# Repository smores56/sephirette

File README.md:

> **Moved.** This board now lives in the [Clog family repo](https://github.com/smores56/clog), under [`sephirette/`](https://github.com/smores56/clog/tree/main/sephirette).

---

The Sephirette
==============

The Sephirette is a split 34-key keyboard with pinky clusters. It is the split
version of the [Osprette MX][osprette-mx], designed by me, which itself was inspired by
the [Balbuzard][balbuzard] by brow.

Follow the [build guide][build-guide] to build your Sephirette.

[osprette-mx]: https://github.com/smores56/osprette-mx
[balbuzard]: https://github.com/brow/balbuzard
[build-guide]: ./doc/buildguide_en.md

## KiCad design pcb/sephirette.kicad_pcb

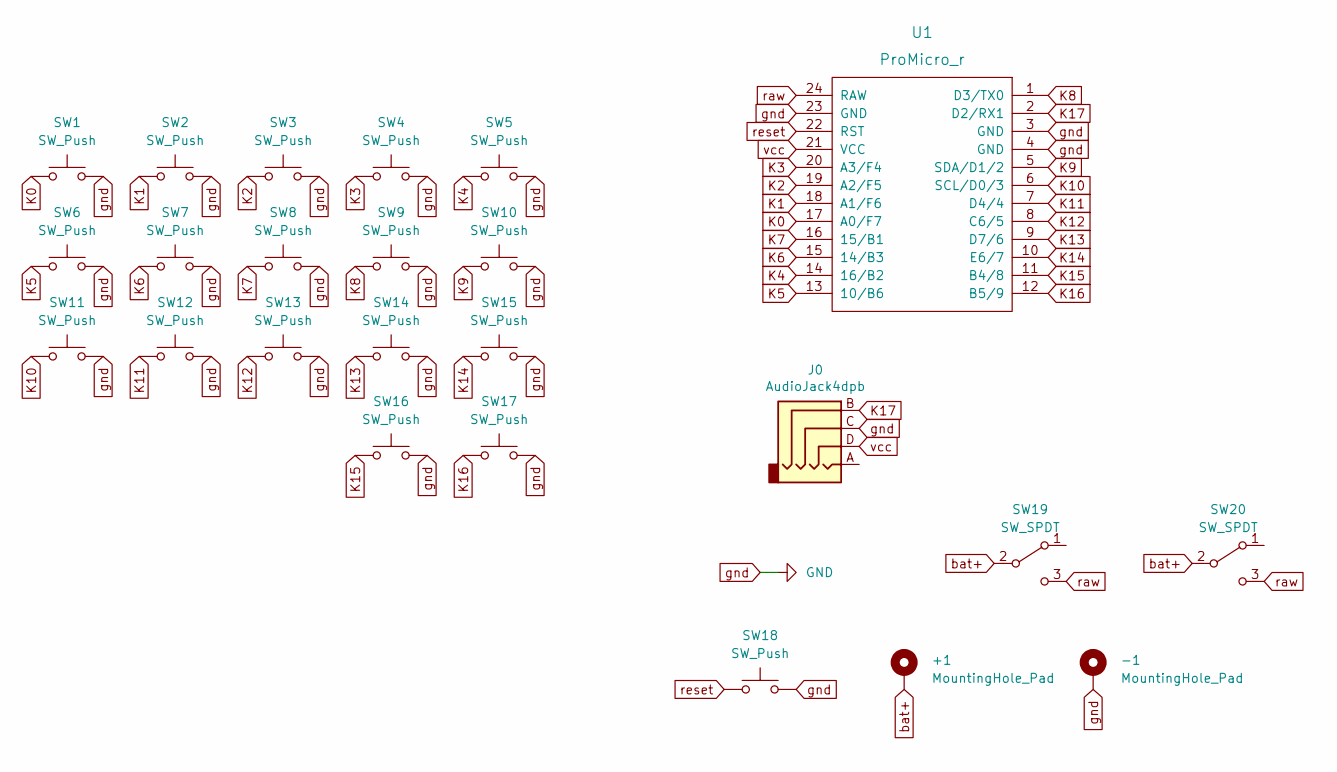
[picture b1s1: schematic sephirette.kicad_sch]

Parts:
+1: MountingHole_Pad; 1pin_conn
-1: MountingHole_Pad; 1pin_conn
J0: AudioJack4dpb; MJ-4PP-9
SW1, SW2, SW3, SW4, SW5, SW6, SW7, SW8, SW9, SW10, SW11, SW12, SW13, SW14, SW15, SW16, SW17: SW_Push; Kailh_socket_MX_optional_reversible
SW18: SW_Push; ResetSW
SW19, SW20: SW_SPDT; SW_SPDT_PCM12
U1: ProMicro_r; ProMicro_v3.5

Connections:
K0: SW1.1, U1.17 (A0/F7)
K1: SW2.1, U1.18 (A1/F6)
K2: SW3.1, U1.19 (A2/F5)
K3: SW4.1, U1.20 (A3/F4)
K4: SW5.1, U1.14 (16/B2)
K5: SW6.1, U1.13 (10/B6)
K6: SW7.1, U1.15 (14/B3)
K7: SW8.1, U1.16 (15/B1)
K8: SW9.1, U1.1 (D3/TX0)
K9: SW10.1, U1.5 (SDA/D1/2)
K10: SW11.1, U1.6 (SCL/D0/3)
K11: SW12.1, U1.7 (D4/4)
K12: SW13.1, U1.8 (C6/5)
K13: SW14.1, U1.9 (D7/6)
K14: SW15.1, U1.10 (E6/7)
K15: SW16.1, U1.11 (B4/8)
K16: SW17.1, U1.12 (B5/9)
K17: J0.B, U1.2 (D2/RX1)
bat+: +1.1, SW19.2 (B), SW20.2 (B); also elsewhere on the board
gnd: -1.1, J0.C, SW1.2, SW2.2, SW3.2, SW4.2, SW5.2, SW6.2, SW7.2, SW8.2, SW9.2, SW10.2, SW11.2, SW12.2, SW13.2, SW14.2, SW15.2, SW16.2, SW17.2, SW18.2, U1.3 (GND), U1.4 (GND), U1.23 (GND); also elsewhere on the board
raw: SW19.3 (C), SW20.3 (C), U1.24 (RAW)
reset: SW18.1, U1.22 (RST)
vcc: J0.D, U1.21 (VCC)

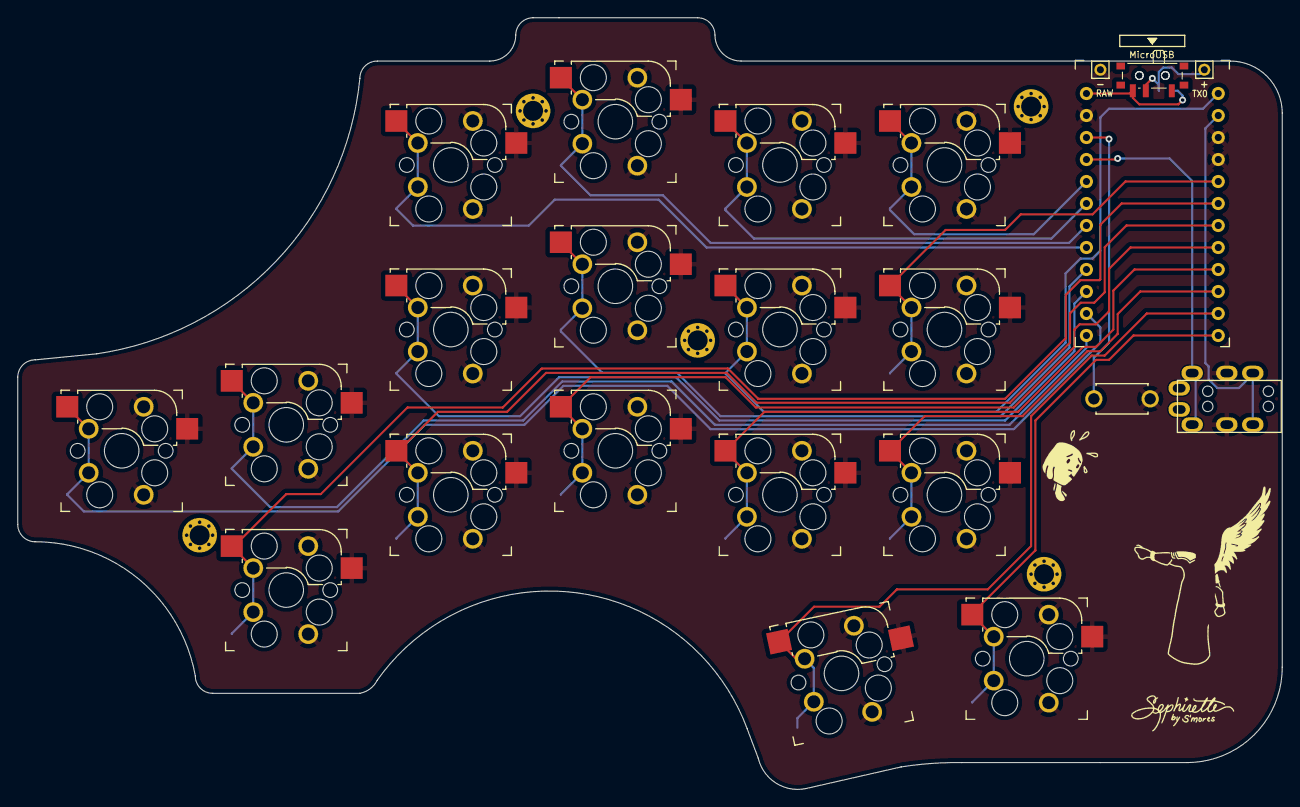
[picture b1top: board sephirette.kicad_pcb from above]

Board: 2 copper layers, 146.0 x 89.1 mm, 29 parts (1 on the bottom side), 23 nets.

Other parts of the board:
+: MountingHole_Pad; 1pin_conn
-: MountingHole_Pad; 1pin_conn
Ref**: Val**; M2_HOLE_v3
Ref**#2, Ref**#3, Ref**#4, Ref**#5: Val**; M2_HOLE_v3

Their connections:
bat+: +.1; also elsewhere on the board
gnd: -.1; also elsewhere on the board

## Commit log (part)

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2022-01-03 added art, created PCB with plate kit
2022-01-23 docs(): add build guide
2022-01-23 Apply suggestions from code review
2022-03-01 docs(): add reference to build guide in README
2022-08-01 Adding CAD models for case
